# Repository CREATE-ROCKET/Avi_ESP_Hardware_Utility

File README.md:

# Avi_ESP_Hardware_Utility

# ESP_Writer_BRD_v1.0.0

https://akizukidenshi.com/catalog/g/gK-01977/

秋月電子のFT232RL USBシリアル変換基板を用いてESPを書き込むことができる基板

FT232RLの3.3vレギュレータとは別のレギュレータをもち，USB電源から3.3v電源を生成する．この電源を用いてマイコンを駆動する場合は基板のスイッチをオンにする．他電源から基板に電力を供給する場合はスイッチをオフにする

# teraterm_macro
teratermにて，ESP_Writer_BRD_v1.0.0 を用いて基板とシリアル通信する場合，このマクロファイルの実行が必要である．

# pio_serial_monitor
teratermにて，ESP_Writer_BRD_v1.0.0 を用いて基板とシリアル通信する場合，platformio.iniの一例を示す．

# 配線

書き込み基板側は，TXDの横のNCピンを潰し，刺し間違えないようにする．

対象基板側はDTRの横のNCピンを潰し，刺し間違えないようにする．

基板側のピンだけでなく，配線コネクタについても溶かして潰すとより良い．

配線は，RXDとTXDを接続，他は同じ物同士を接続する．

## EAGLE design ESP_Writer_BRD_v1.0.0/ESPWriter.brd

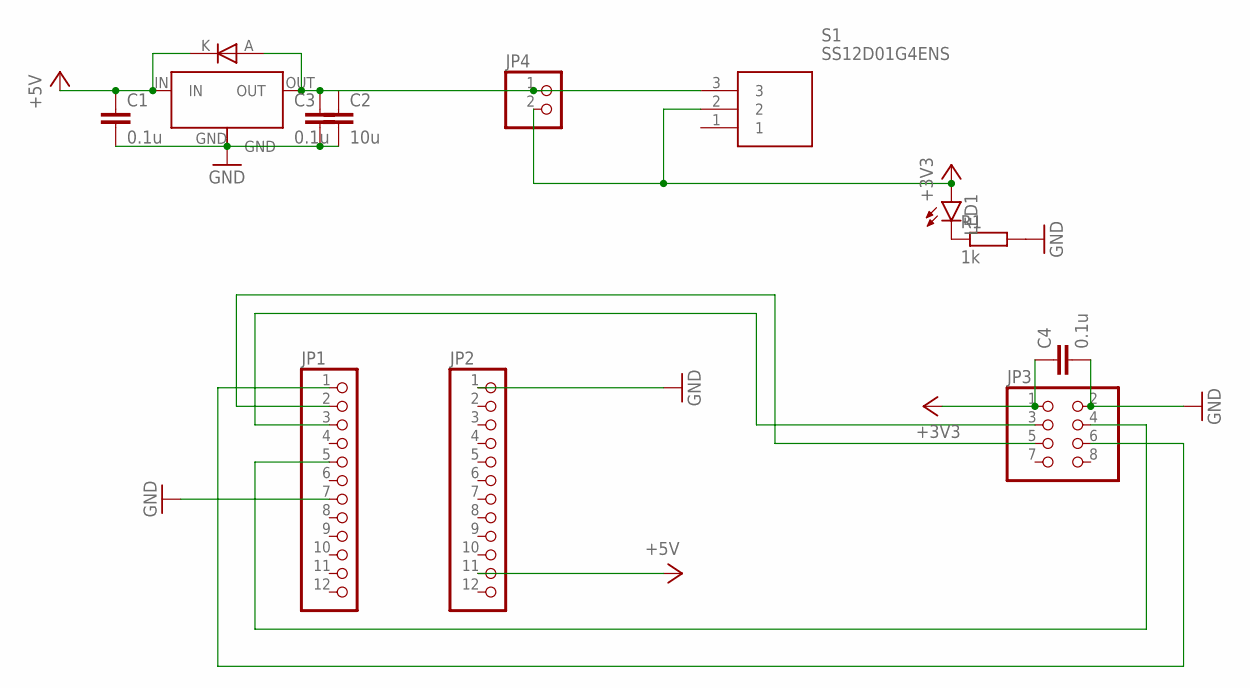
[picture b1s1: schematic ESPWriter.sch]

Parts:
C1, C3, C4: 0.1u; C0603
C2: 10u; C0603
JP1, JP2: PINHD-1X12; 1X12
JP3: PINHD-2X4; 2X04
JP4: PINHD-1X2; 1X02
LED1: LEDCHIPLED_0603; CHIPLED_0603
R1: 1k; R0603
S1: SS12D01G4ENS; SS12D01G4
U$5: 3v3 reg; NJM2391DL1-33
U$6: SS2040FL

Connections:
+3V3: C4.1, JP3.1, JP4.2, LED1.A, S1.2
+5V: C1.1, JP2.11, U$5.IN, U$6.K
GND: C1.2, C2.2, C3.2, C4.2, JP1.7, JP2.1, JP3.2, R1.2, U$5.GND
unnamed: C2.1, C3.1, JP4.1, S1.3, U$5.OUT, U$6.A
unnamed: JP1.3, JP3.3
unnamed: JP1.2, JP3.5
unnamed: JP1.5, JP3.4
unnamed: JP1.1, JP3.6
unnamed: LED1.C, R1.1

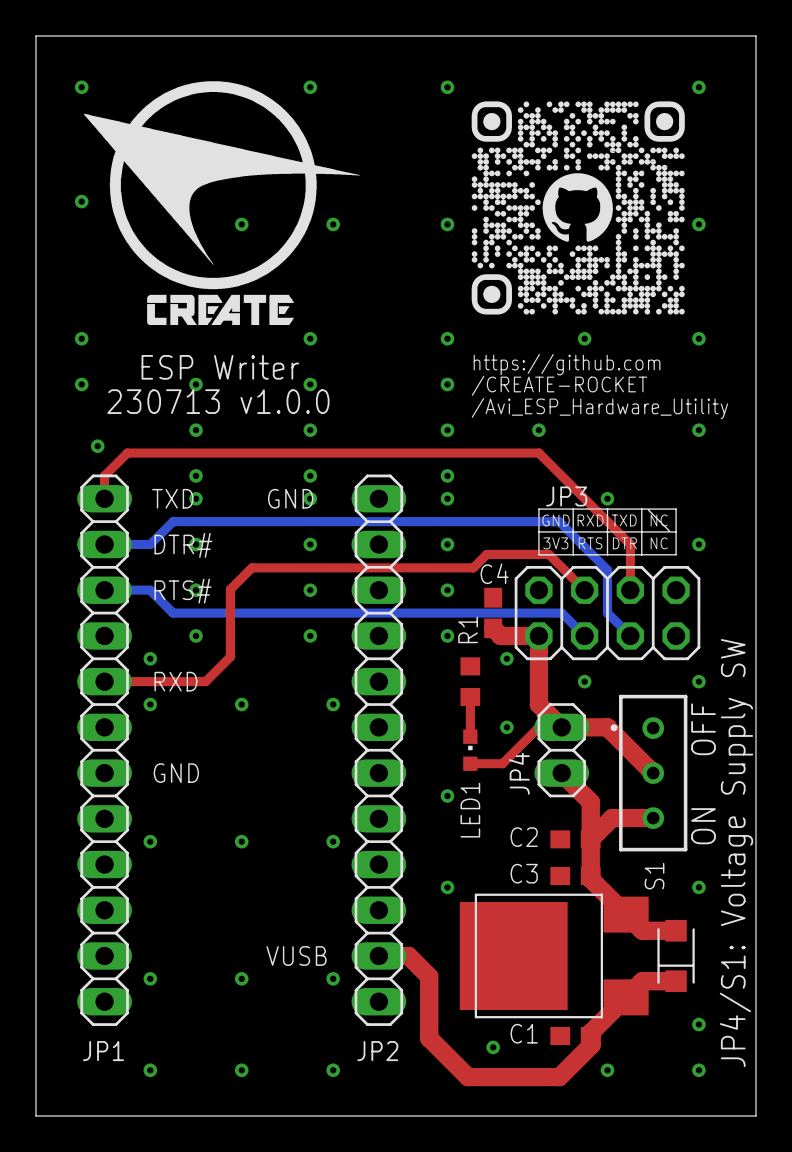
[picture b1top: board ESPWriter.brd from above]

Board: 2 copper layers, 40.0 x 60.0 mm, 13 parts (0 on the bottom side), 9 nets.

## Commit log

2023-07-13 add writer board
2023-07-13 update board
